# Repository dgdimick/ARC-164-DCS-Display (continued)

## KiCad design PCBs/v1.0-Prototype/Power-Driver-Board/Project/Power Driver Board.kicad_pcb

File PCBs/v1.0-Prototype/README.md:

# ARC-164 PCB Version 1.0 — Prototype

**Last updated: November 10, 2026 at 5:45 PM MST (America/Denver)**

**LED Sub Board v1.2 is now published for Main Board v1.2.** I printed the latest mockup at **100%** and it passed the fit test, including **frequency and channel LED alignment and J20 connector/cable clearance**. The final layout keeps the **FREQ LEDs up 0.5 mm**, the **channel LEDs up 0.5 mm with their earlier 0.5 mm leftward adjustment**, and **J20 up 2 mm total** from the previous mounting position. The **0.75 mm gaps, 6 mm display bodies and tested 8 mm mounting stack** remain unchanged. **Use Main Board v1.2 with LED Sub Board v1.2; older Sub Boards do not match this Main Board. Assembled electrical testing is still pending.**

Initial public three-board PCB prototype revision, November 7, 2026. These are untested prototypes, not assembled or production-validated hardware. [GitHub prototype release](https://github.com/dgdimick/ARC-164-DCS-Display/releases/tag/pcb-v1.0-prototype).

| Board | Source | Fabrication data | Schematic | BOM |
| --- | --- | --- | --- | --- |
| Main Board v1.0 | Withdrawn; [current Main Board v1.2](../v1.2/Main-Board/README.md) uses the [matching Sub Board v1.2](../v1.2/LED-Subboard/README.md) | — | — | — |
| Power Driver Board | [KiCad project](Power-Driver-Board/Project/Power%20Driver%20Board.kicad_pro) | [Gerbers and drills](Power-Driver-Board/Manufacturing/) | [PDF](Power-Driver-Board/Schematics/Power-Driver-Board-v1.0-Prototype.pdf) | [CSV](Power-Driver-Board/Assembly/BOM.csv) |
| LED Subboard v1.0 | Withdrawn; use [Sub Board v1.2](../v1.2/LED-Subboard/README.md) with Main Board v1.2 | — | — | — |

Open the project in KiCad 10.0.7 or newer. Each project includes its used footprint libraries, custom symbols and all referenced 3D models with project-relative paths. BOMs are schematic-generated component lists; sockets, Teensy headers and cables are additional assembly items described in the documentation.

## Required reading

- [Current three-board wiring, all cable pinouts and Teensy GPIO mapping](Docs/Wiring.md)
- [Assembly order and orientation checks](Docs/Assembly.md)
- [Known issues and validation limits](Docs/Known-Issues.md)
- [Electrical connector audit](Docs/Electrical-Audit.json)
- [Connector comparison](Docs/Connector-Pin-Comparison.csv)

## Prototype limitations

**At the original v1.0 release, all three boards had zero DRC violations, zero unconnected items, and zero schematic parity issues; all three schematics passed ERC.** These historical checks do not establish compatibility with Main Board v1.2 or validate the unfinished matching Sub Board. D17 was moved clear of SW7’s courtyard, and Main Board routing and both GND fills were rebuilt. Library warnings and D12 silkscreen clipping were corrected without moving components, outlines or holes.

All manufactured-board electrical tests, actual cable/connector fit, socket/stack clearance and firmware integration remain to be performed. Review these limits before ordering. Use the supplied board version as a prototype baseline; this is not a production sign-off.

The manufacturing folders contain two-layer Gerbers (front/back copper, solder mask and silkscreen, plus Edge.Cuts) and separate plated/non-plated Excellon drill files where applicable. Routed holes/cutouts remain in Edge.Cuts; oblong strain-relief slots are included in drill data. Board thickness is recorded in each KiCad project. Confirm the manufacturer’s preview before ordering.

See the included project licenses. The models retain their source provenance; standard KiCad assets follow their library licenses.

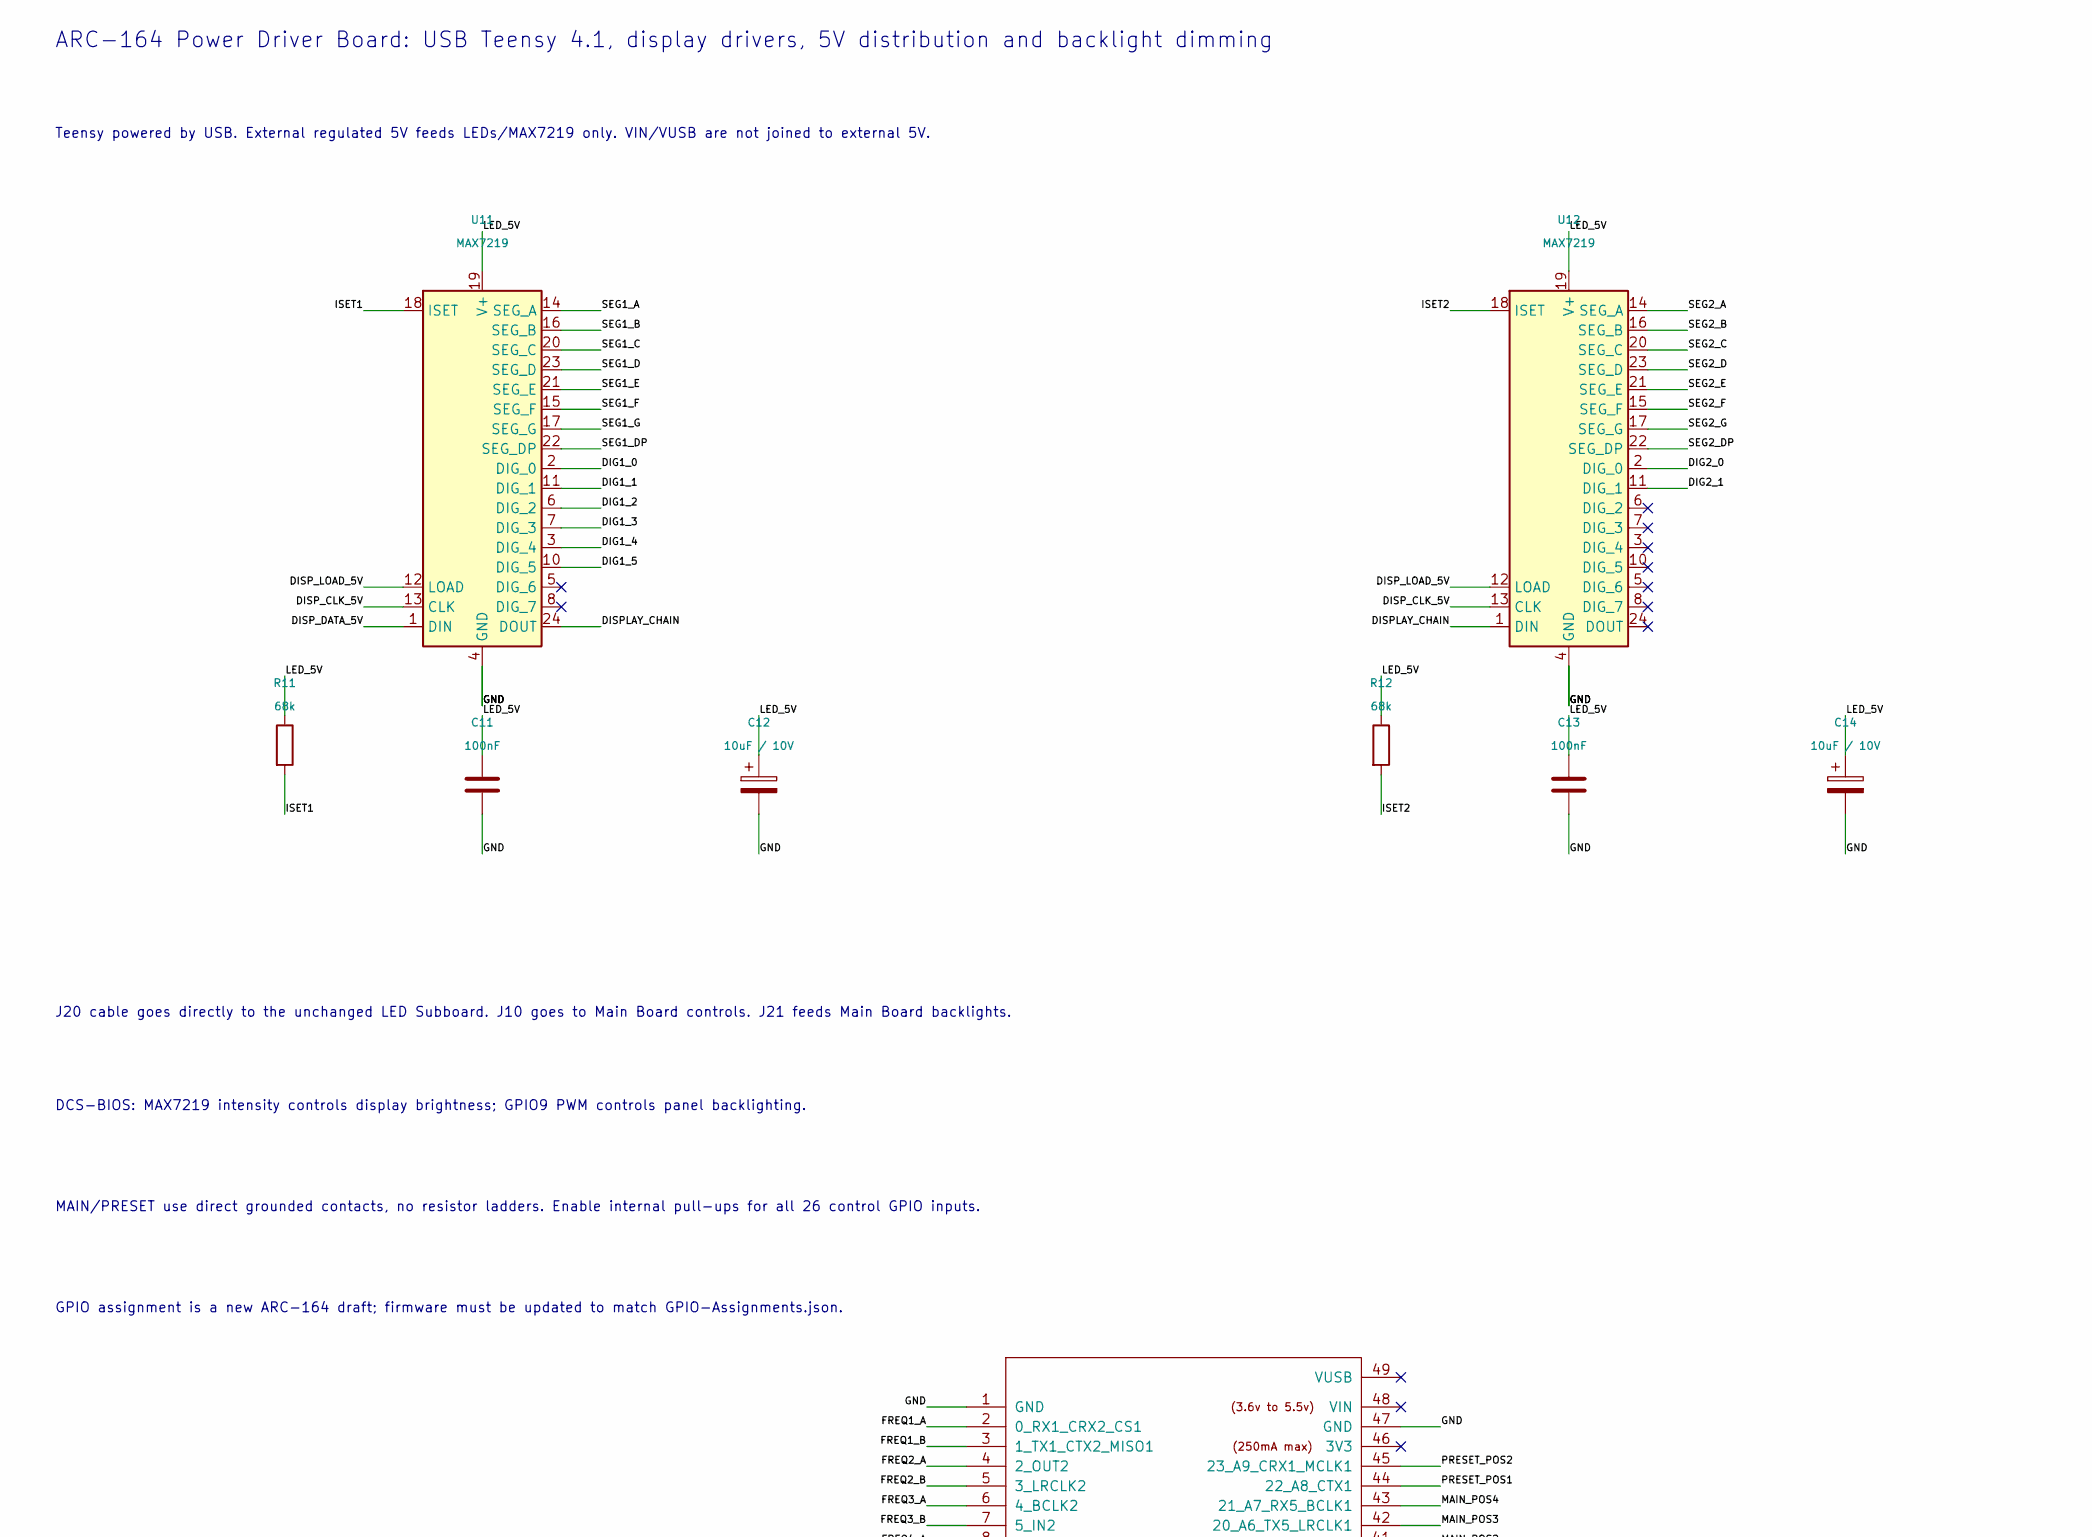
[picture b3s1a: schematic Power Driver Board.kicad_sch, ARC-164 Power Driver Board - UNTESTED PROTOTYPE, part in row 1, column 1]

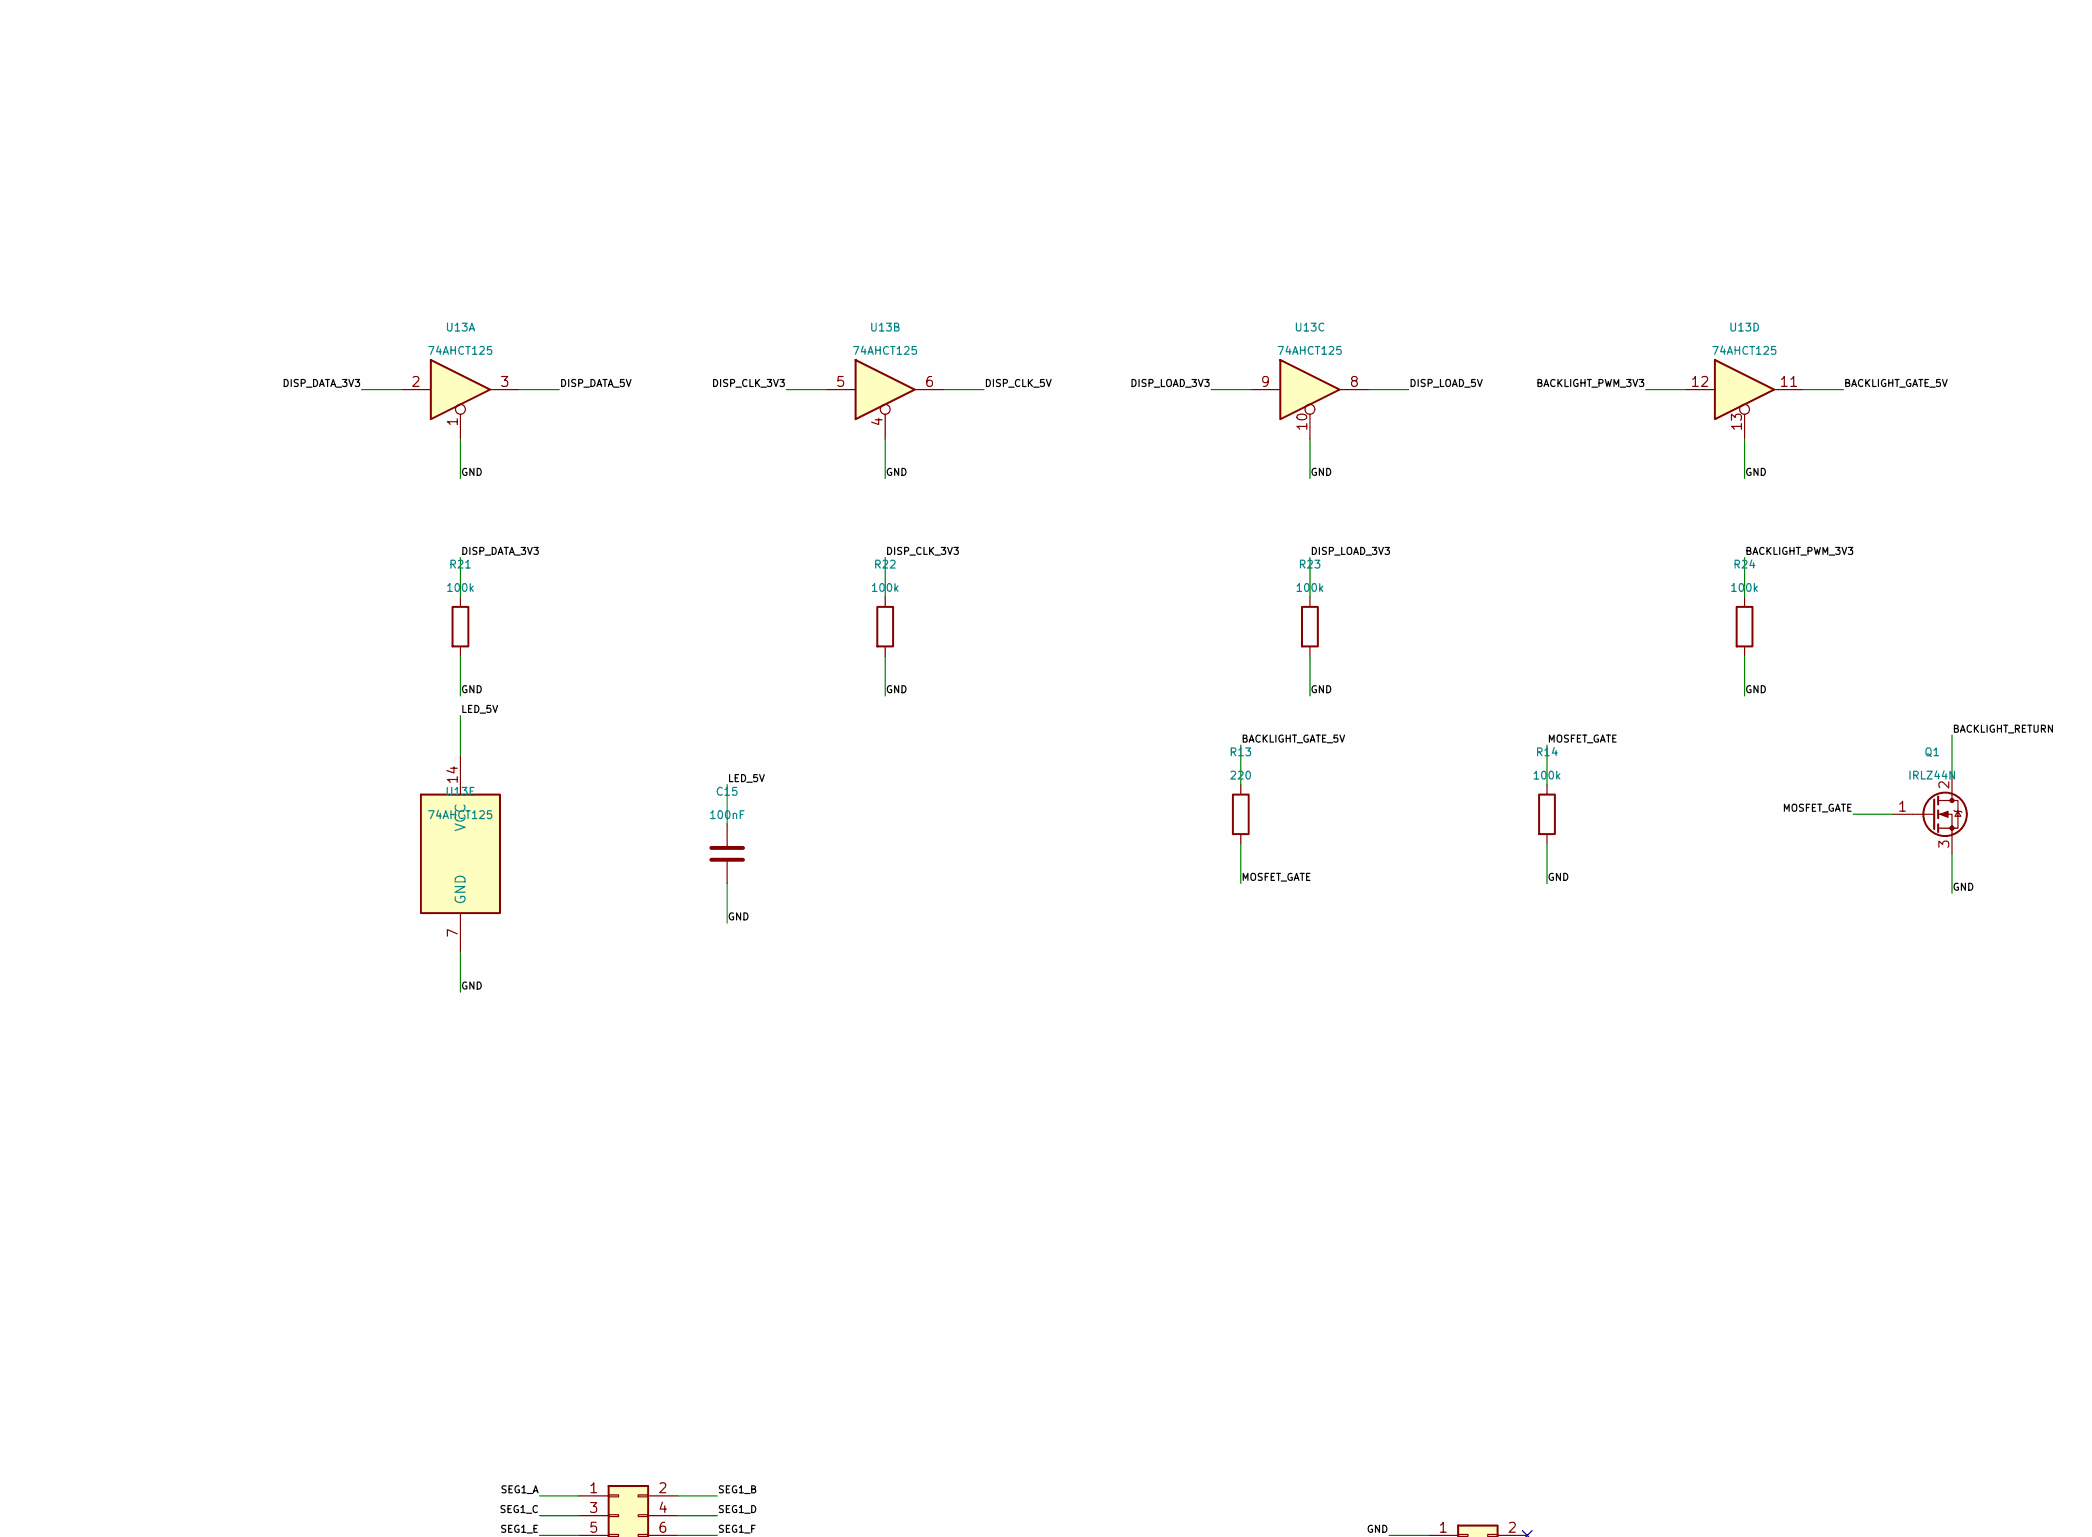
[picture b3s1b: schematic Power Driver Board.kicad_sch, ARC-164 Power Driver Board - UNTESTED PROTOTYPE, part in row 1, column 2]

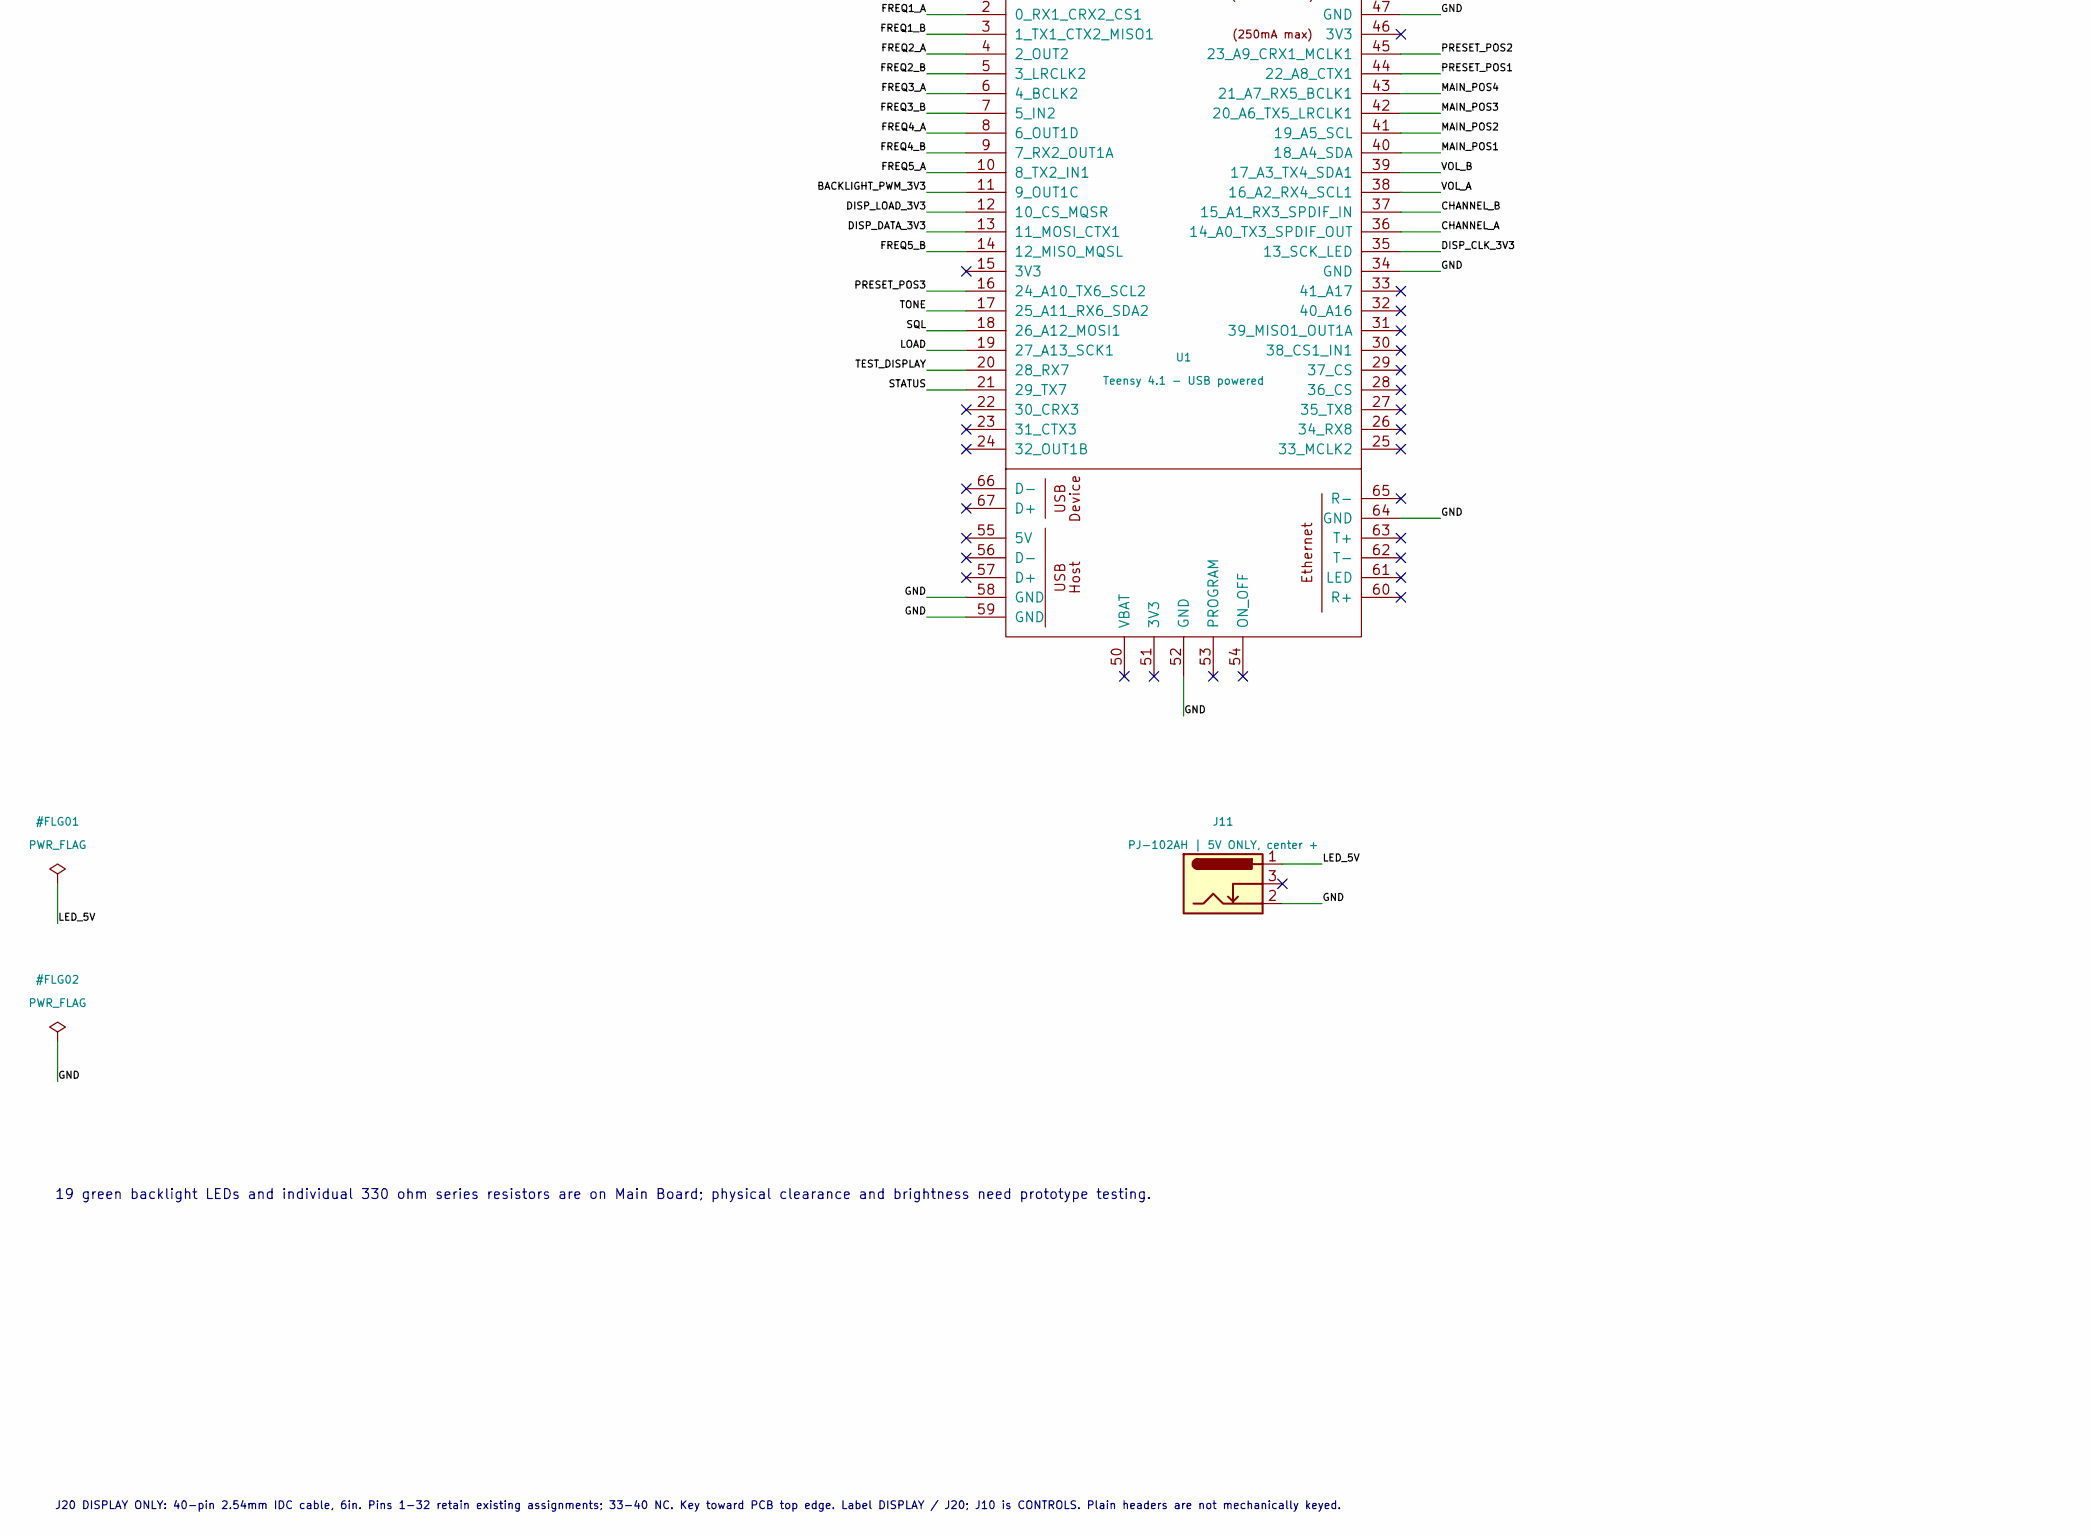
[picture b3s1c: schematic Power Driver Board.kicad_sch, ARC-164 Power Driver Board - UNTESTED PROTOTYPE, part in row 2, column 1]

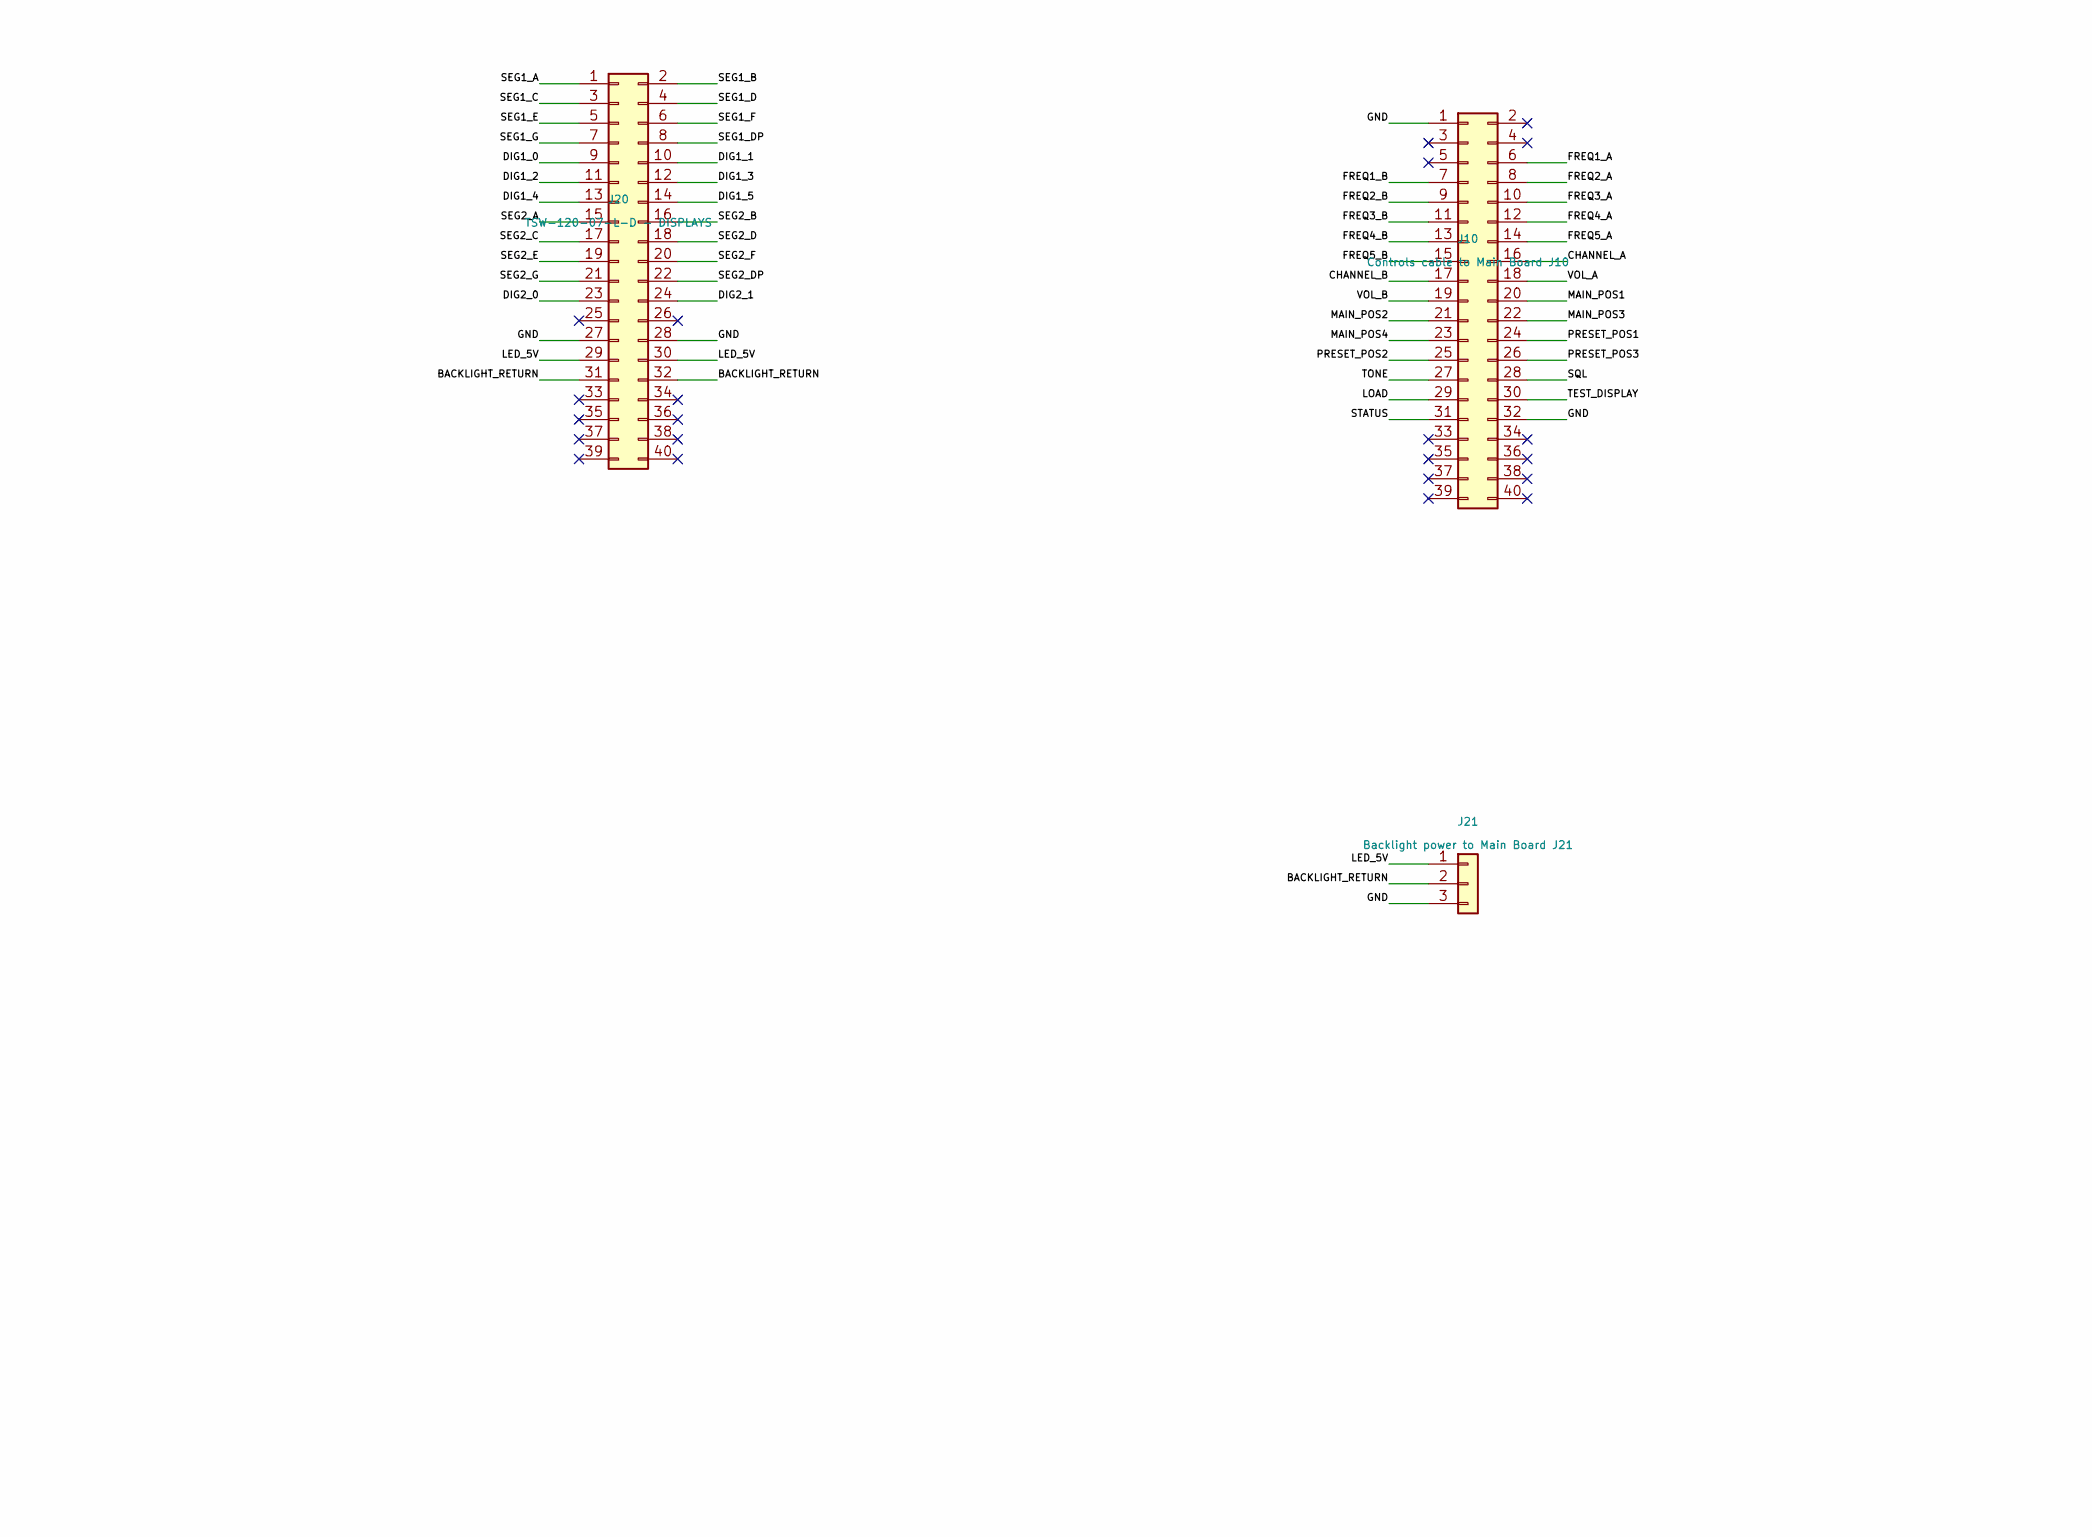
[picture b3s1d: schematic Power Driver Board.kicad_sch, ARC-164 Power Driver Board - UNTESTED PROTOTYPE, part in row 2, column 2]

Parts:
C11, C13, C15: 100nF; C_Disc_D5.0mm_W2.5mm_P5.00mm
C12, C14: 10uF / 10V; CP_Radial_D5.0mm_P2.00mm
J10: Controls cable to Main Board J10; PinHeader_2x20_P2.54mm_Vertical
J11: PJ-102AH | 5V ONLY, center +; BarrelJack_CUI_PJ-102AH_Horizontal
J20: TSW-120-07-L-D - DISPLAYS; PinHeader_2x20_P2.54mm_Vertical
J21: Backlight power to Main Board J21; PinHeader_1x03_P2.54mm_Vertical
Q1: IRLZ44N; TO-220-3_Vertical
R11, R12: 68k; R_Axial_DIN0207_L6.3mm_D2.5mm_P10.16mm_Horizontal
R13: 220; R_Axial_DIN0207_L6.3mm_D2.5mm_P10.16mm_Horizontal
R14, R21, R22, R23, R24: 100k; R_Axial_DIN0207_L6.3mm_D2.5mm_P10.16mm_Horizontal
U1: Teensy 4.1 - USB powered; Teensy41
U11, U12: MAX7219; DIP-24_W7.62mm
U13: 74AHCT125; DIP-14_W7.62mm

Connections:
/BACKLIGHT_GATE_5V: R13.1, U13.11
/BACKLIGHT_PWM_3V3: R24.1, U1.11 (9_OUT1C), U13.12
/BACKLIGHT_RETURN: J20.31, J20.32, J21.2, Q1.2 (D)
/CHANNEL_A: J10.16, U1.36 (14_A0_TX3_SPDIF_OUT)
/CHANNEL_B: J10.17, U1.37 (15_A1_RX3_SPDIF_IN)
/DIG1_0: J20.9, U11.2 (DIG_0)
/DIG1_1: J20.10, U11.11 (DIG_1)
/DIG1_2: J20.11, U11.6 (DIG_2)
/DIG1_3: J20.12, U11.7 (DIG_3)
/DIG1_4: J20.13, U11.3 (DIG_4)
/DIG1_5: J20.14, U11.10 (DIG_5)
/DIG2_0: J20.23, U12.2 (DIG_0)
/DIG2_1: J20.24, U12.11 (DIG_1)
/DISPLAY_CHAIN: U11.24 (DOUT), U12.1 (DIN)
/DISP_CLK_3V3: R22.1, U1.35 (13_SCK_LED), U13.5
/DISP_CLK_5V: U11.13 (CLK), U12.13 (CLK), U13.6
/DISP_DATA_3V3: R21.1, U1.13 (11_MOSI_CTX1), U13.2
/DISP_DATA_5V: U11.1 (DIN), U13.3
/DISP_LOAD_3V3: R23.1, U1.12 (10_CS_MQSR), U13.9
/DISP_LOAD_5V: U11.12 (LOAD), U12.12 (LOAD), U13.8
/FREQ1_A: J10.6, U1.2 (0_RX1_CRX2_CS1)
/FREQ1_B: J10.7, U1.3 (1_TX1_CTX2_MISO1)
/FREQ2_A: J10.8, U1.4 (2_OUT2)
/FREQ2_B: J10.9, U1.5 (3_LRCLK2)
/FREQ3_A: J10.10, U1.6 (4_BCLK2)
/FREQ3_B: J10.11, U1.7 (5_IN2)
/FREQ4_A: J10.12, U1.8 (6_OUT1D)
/FREQ4_B: J10.13, U1.9 (7_RX2_OUT1A)
/FREQ5_A: J10.14, U1.10 (8_TX2_IN1)
/FREQ5_B: J10.15, U1.14 (12_MISO_MQSL)
/GND: C11.2, C12.2, C13.2, C14.2, C15.2, J10.1, J10.32, J11.2, J20.27, J20.28, J21.3, Q1.3 (S), R14.2, R21.2, R22.2, R23.2, R24.2, U1.1 (GND), U1.34 (GND), U1.47 (GND), U1.52 (GND), U1.58 (GND), U1.59 (GND), U1.64 (GND), U11.4 (GND), U11.9 (GND), U12.4 (GND), U12.9 (GND), U13.1, U13.4, U13.7 (GND), U13.10, U13.13
/ISET1: R11.2, U11.18 (ISET)
/ISET2: R12.2, U12.18 (ISET)
/LED_5V: C11.1, C12.1, C13.1, C14.1, C15.1, J11.1, J20.29, J20.30, J21.1, R11.1, R12.1, U11.19 (V+), U12.19 (V+), U13.14 (VCC)
/LOAD: J10.29, U1.19 (27_A13_SCK1)
/MAIN_POS1: J10.20, U1.40 (18_A4_SDA)
/MAIN_POS2: J10.21, U1.41 (19_A5_SCL)
/MAIN_POS3: J10.22, U1.42 (20_A6_TX5_LRCLK1)
/MAIN_POS4: J10.23, U1.43 (21_A7_RX5_BCLK1)
/MOSFET_GATE: Q1.1 (G), R13.2, R14.1
/PRESET_POS1: J10.24, U1.44 (22_A8_CTX1)
/PRESET_POS2: J10.25, U1.45 (23_A9_CRX1_MCLK1)
/PRESET_POS3: J10.26, U1.16 (24_A10_TX6_SCL2)
/SEG1_A: J20.1, U11.14 (SEG_A)
/SEG1_B: J20.2, U11.16 (SEG_B)
/SEG1_C: J20.3, U11.20 (SEG_C)
/SEG1_D: J20.4, U11.23 (SEG_D)
/SEG1_DP: J20.8, U11.22 (SEG_DP)
/SEG1_E: J20.5, U11.21 (SEG_E)
/SEG1_F: J20.6, U11.15 (SEG_F)
/SEG1_G: J20.7, U11.17 (SEG_G)
/SEG2_A: J20.15, U12.14 (SEG_A)
/SEG2_B: J20.16, U12.16 (SEG_B)
/SEG2_C: J20.17, U12.20 (SEG_C)
/SEG2_D: J20.18, U12.23 (SEG_D)
/SEG2_DP: J20.22, U12.22 (SEG_DP)
/SEG2_E: J20.19, U12.21 (SEG_E)
/SEG2_F: J20.20, U12.15 (SEG_F)
/SEG2_G: J20.21, U12.17 (SEG_G)
/SQL: J10.28, U1.18 (26_A12_MOSI1)
/STATUS: J10.31, U1.21 (29_TX7)
/TEST_DISPLAY: J10.30, U1.20 (28_RX7)
/TONE: J10.27, U1.17 (25_A11_RX6_SDA2)
/VOL_A: J10.18, U1.38 (16_A2_RX4_SCL1)
/VOL_B: J10.19, U1.39 (17_A3_TX4_SDA1)

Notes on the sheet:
ARC-164 Power Driver Board: USB Teensy 4.1, display drivers, 5V distribution and backlight dimming
Teensy powered by USB. External regulated 5V feeds LEDs/MAX7219 only. VIN/VUSB are not joined to external 5V.
J20 cable goes directly to the unchanged LED Subboard. J10 goes to Main Board controls. J21 feeds Main Board backlights.
DCS-BIOS: MAX7219 intensity controls display brightness; GPIO9 PWM controls panel backlighting.
MAIN/PRESET use direct grounded contacts, no resistor ladders. Enable internal pull-ups for all 26 control GPIO inputs.
GPIO assignment is a new ARC-164 draft; firmware must be updated to match GPIO-Assignments.json.
19 green backlight LEDs and individual 330 ohm series resistors are on Main Board; physical clearance and brightness need prototype testing.
J20 DISPLAY ONLY: 40-pin 2.54mm IDC cable, 6in. Pins 1-32 retain existing assignments; 33-40 NC. Key toward PCB top edge. Label DISPLAY / J20; J10 is CONTROLS. Plain headers are not mechanically keyed.

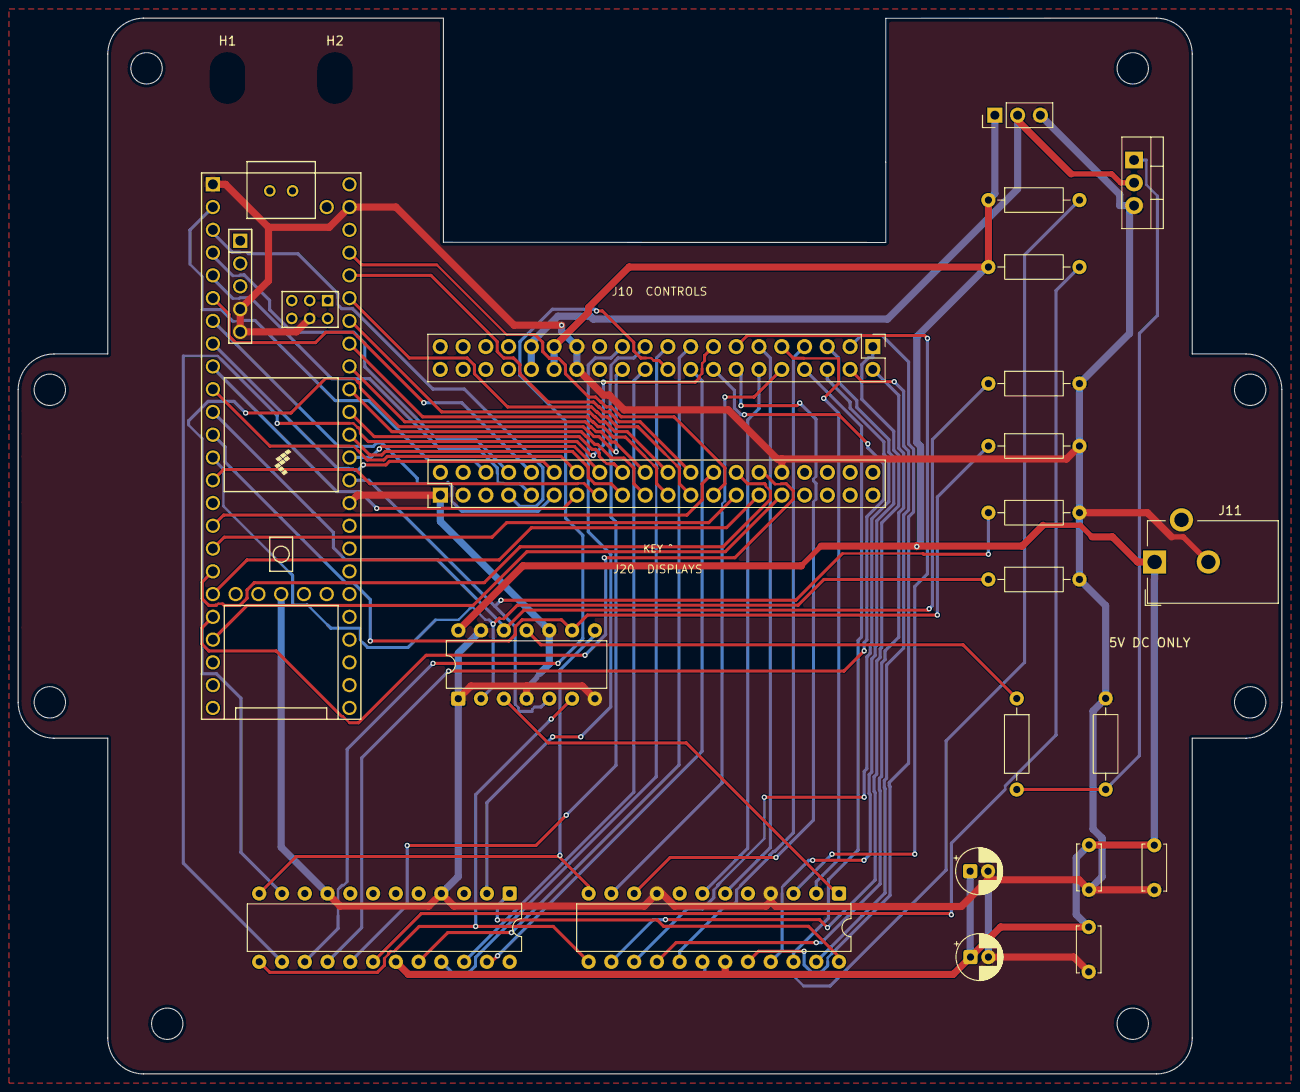
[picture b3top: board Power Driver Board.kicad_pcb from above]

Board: 2 copper layers, 141.0 x 117.8 mm, 24 parts (0 on the bottom side), 65 nets.

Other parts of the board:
H1, H2: USB strain relief 3.2x5mm slot; USB_Strain_Relief_Slot_3.2x5mm

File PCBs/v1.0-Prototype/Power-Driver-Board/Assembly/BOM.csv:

"Refs","Value","Footprint","Qty","DNP"
"C11,C13,C15","100nF","Capacitor_THT:C_Disc_D5.0mm_W2.5mm_P5.00mm","3",""
"C12,C14","10uF / 10V","Capacitor_THT:CP_Radial_D5.0mm_P2.00mm","2",""
"J10","Controls cable to Main Board J10","Connector_PinHeader_2.54mm:PinHeader_2x20_P2.54mm_Vertical","1",""
"J11","PJ-102AH | 5V ONLY, center +","ARC164_Power:BarrelJack_CUI_PJ-102AH_Horizontal","1",""
"J20","TSW-120-07-L-D - DISPLAYS","Connector_PinHeader_2.54mm:PinHeader_2x20_P2.54mm_Vertical","1",""
"J21","Backlight power to Main Board J21","Connector_PinHeader_2.54mm:PinHeader_1x03_P2.54mm_Vertical","1",""
"Q1","IRLZ44N","Package_TO_SOT_THT:TO-220-3_Vertical","1",""
"R11,R12","68k","Resistor_THT:R_Axial_DIN0207_L6.3mm_D2.5mm_P10.16mm_Horizontal","2",""
"R13","220","Resistor_THT:R_Axial_DIN0207_L6.3mm_D2.5mm_P10.16mm_Horizontal","1",""
"R14,R21-R24","100k","Resistor_THT:R_Axial_DIN0207_L6.3mm_D2.5mm_P10.16mm_Horizontal","5",""
"U1","Teensy 4.1 - USB powered","teensy:Teensy41","1",""
"U11,U12","MAX7219","Package_DIP:DIP-24_W7.62mm","2",""
"U13","74AHCT125","Package_DIP:DIP-14_W7.62mm","1",""

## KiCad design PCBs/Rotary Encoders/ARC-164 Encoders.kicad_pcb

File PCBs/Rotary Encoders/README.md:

# ARC-164 Rotary Encoder PCB and schematic

**Last updated: October 31, 2026 at 6:19 PM MDT (America/Denver)**

The **ARC-164 encoder PCB v1.1** combines all five frequency encoders and the preset-channel encoder on one board. The layout is routed and includes a front-copper GND pour. **I still need to check mechanical clearances and test-fit the board before ordering PCBs.**

*ARC-164 Encoder PCB — KiCad 3D view. Click to enlarge. Clearance checks and test fitting are still pending.*

## Open the project

Download this folder and keep its contents together. Open [ARC-164 Encoders.kicad_pro](ARC-164%20Encoders.kicad_pro) in KiCad 10, then open the schematic or PCB:

- [Schematic](ARC-164%20Encoders.kicad_sch)
- [PCB layout](ARC-164%20Encoders.kicad_pcb)

The custom symbol library, footprint library, library tables, and PEC11H STEP model are included. The reused library names still begin with ARC210; their paths are relative to this project. KiCad's standard libraries are also needed. I have not included the faceplate drawing, drawing-based pictures, or its reference geometry in these published files.

## Encoders and connections

I placed SW1–SW5 at the five frequency-control positions, left to right, and SW6 at the preset-channel position. The footprint origin is offset from the shaft center; that offset is included in the placement. Frequency centers are 26 mm apart, assuming the supplied drawing is in millimeters. I still need to confirm the drawing scale against the actual faceplate.

All six encoders use Bourns PEC11H-4220F-S0024 footprints. Their C contacts, mounting tabs, and J1 pins 13–14 connect to GND. I corrected the copied schematic's separate common-contact net so the contacts connect to the ground pour. The push-switch contacts remain deliberately unused. ARC-164 Teensy GPIO assignments are not finalized.

| J1 pin | Connection |
| --- | --- |
| 1 | SW1 B |
| 2 | SW1 A |
| 3 | SW2 A |
| 4 | SW2 B |
| 5 | SW3 B |
| 6 | SW3 A |
| 7 | SW4 A |
| 8 | SW4 B |
| 9 | SW5 B |
| 10 | SW5 A |
| 11 | SW6 B |
| 12 | SW6 A |
| 13–14 | GND |

## Validation and remaining checks

Fresh KiCad checks for v1.1 on October 31, 2026 reported **zero ERC violations, zero non-excluded DRC violations, zero unconnected items, and zero schematic/PCB parity issues** under the project's saved settings. The copper zone was refilled before the PCB check. Reports are in [Checks](Checks/). Passing these electrical checks does not establish mechanical fit or a manufacturing-ready design.

I still need to check the actual faceplate dimensions, encoder shaft height and spacers, switch bodies and terminals beside the narrow board section, display hardware, connector and cable access, PCB mounting/support, and 3D model alignment. I will review the layout and run fresh checks again before generating manufacturing files. Gerbers are not included with this version.

[Back to the main README](../../README.md#encoder-pcb-plan)

## Version 1.1 — October 31, 2026

I removed an extra front-copper zone that had no net assigned and was overriding the existing GND pour, causing an isolated-copper violation. I retained and refilled the GND zone, then updated the PCB silkscreen and PCB/schematic revisions to **1.1**. Fresh ERC and DRC checks reported zero violations, zero unconnected items, and zero schematic parity issues under the saved project settings. **Mechanical clearance checks, test fitting, and assembled-board testing remain pending.**

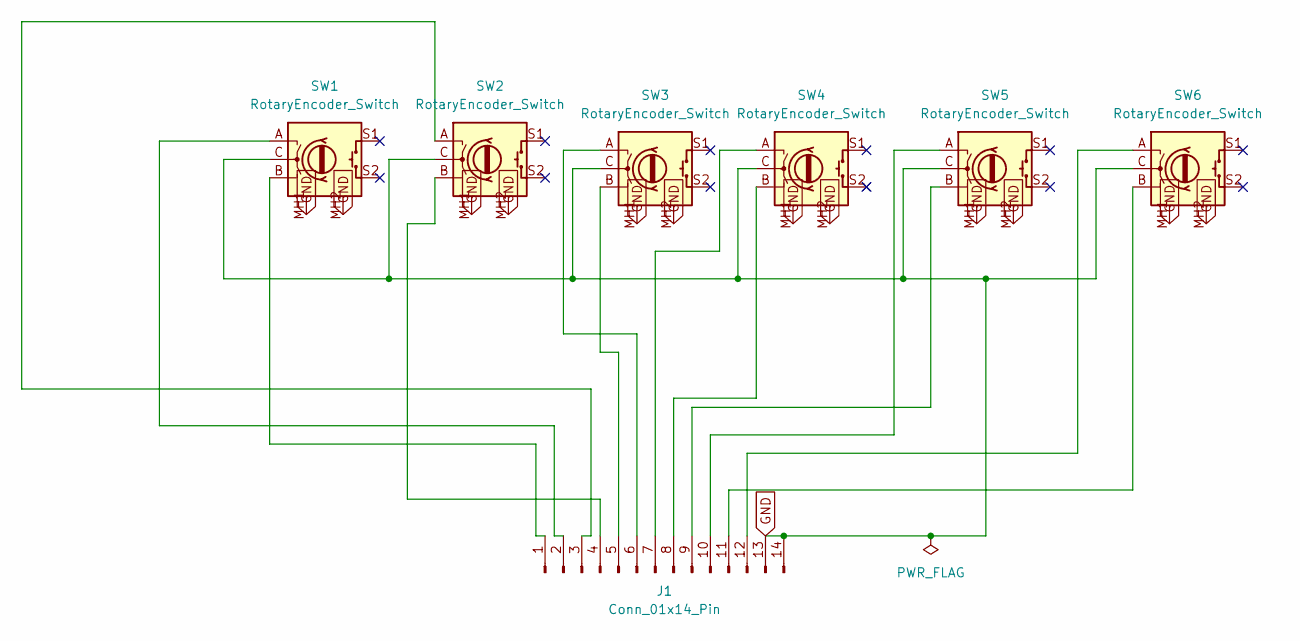
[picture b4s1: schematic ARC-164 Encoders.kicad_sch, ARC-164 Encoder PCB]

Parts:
J1: Conn_01x14_Pin; PinHeader_1x14_P2.54mm_Vertical
SW1, SW2, SW3, SW4, SW5, SW6: RotaryEncoder_Switch; PEC11H4220FS0024

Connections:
GND: J1.13, J1.14, SW1.C, SW1.MH1 (CASE), SW1.MH2 (CASE), SW2.C, SW2.MH1 (CASE), SW2.MH2 (CASE), SW3.C, SW3.MH1 (CASE), SW3.MH2 (CASE), SW4.C, SW4.MH1 (CASE), SW4.MH2 (CASE), SW5.C, SW5.MH1 (CASE), SW5.MH2 (CASE), SW6.C, SW6.MH1 (CASE), SW6.MH2 (CASE)
unnamed: J1.1, SW1.B
unnamed: J1.2, SW1.A
unnamed: J1.3, SW2.A
unnamed: J1.4, SW2.B
unnamed: J1.5, SW3.B
unnamed: J1.6, SW3.A
unnamed: J1.7, SW4.A
unnamed: J1.8, SW4.B
unnamed: J1.9, SW5.B
unnamed: J1.10, SW5.A
unnamed: J1.11, SW6.B
unnamed: J1.12, SW6.A

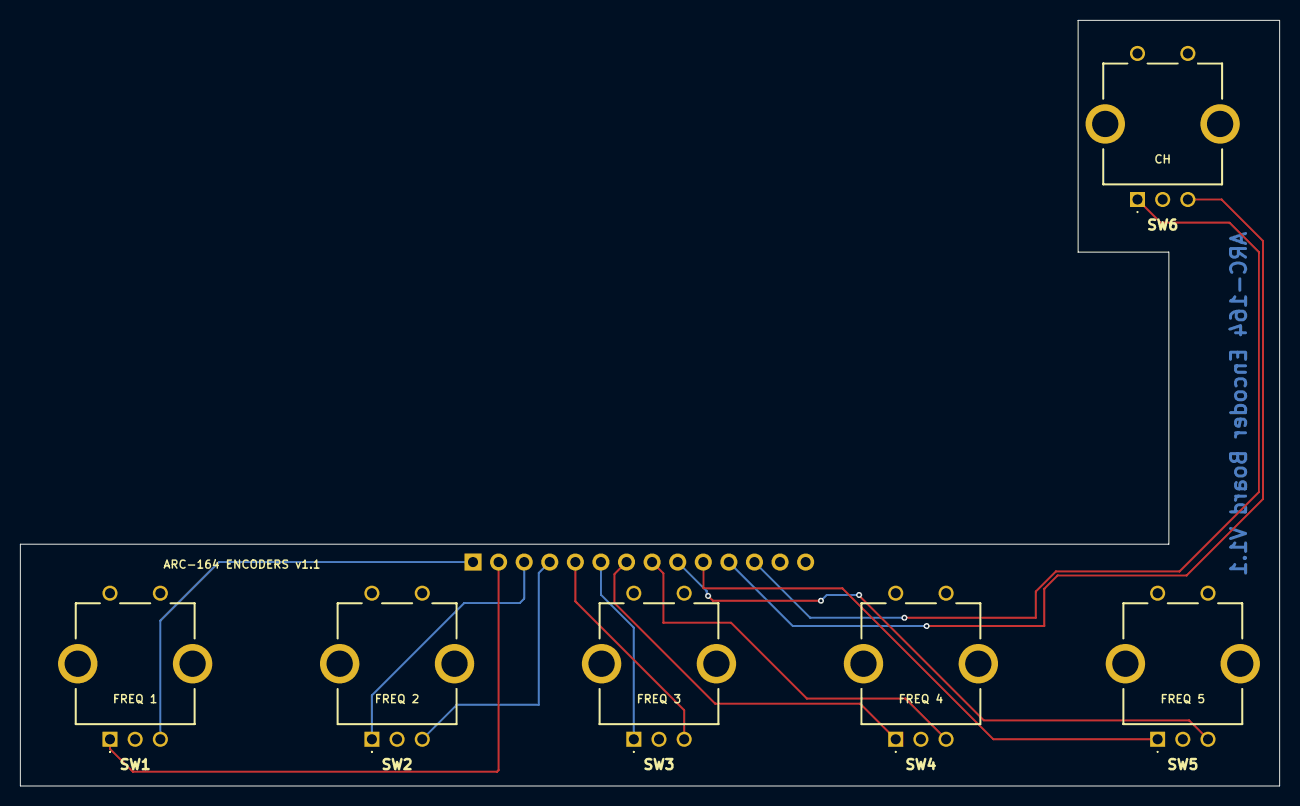
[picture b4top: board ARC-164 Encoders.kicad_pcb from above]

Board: 2 copper layers, 125.0 x 76.0 mm, 7 parts (1 on the bottom side), 13 nets.
